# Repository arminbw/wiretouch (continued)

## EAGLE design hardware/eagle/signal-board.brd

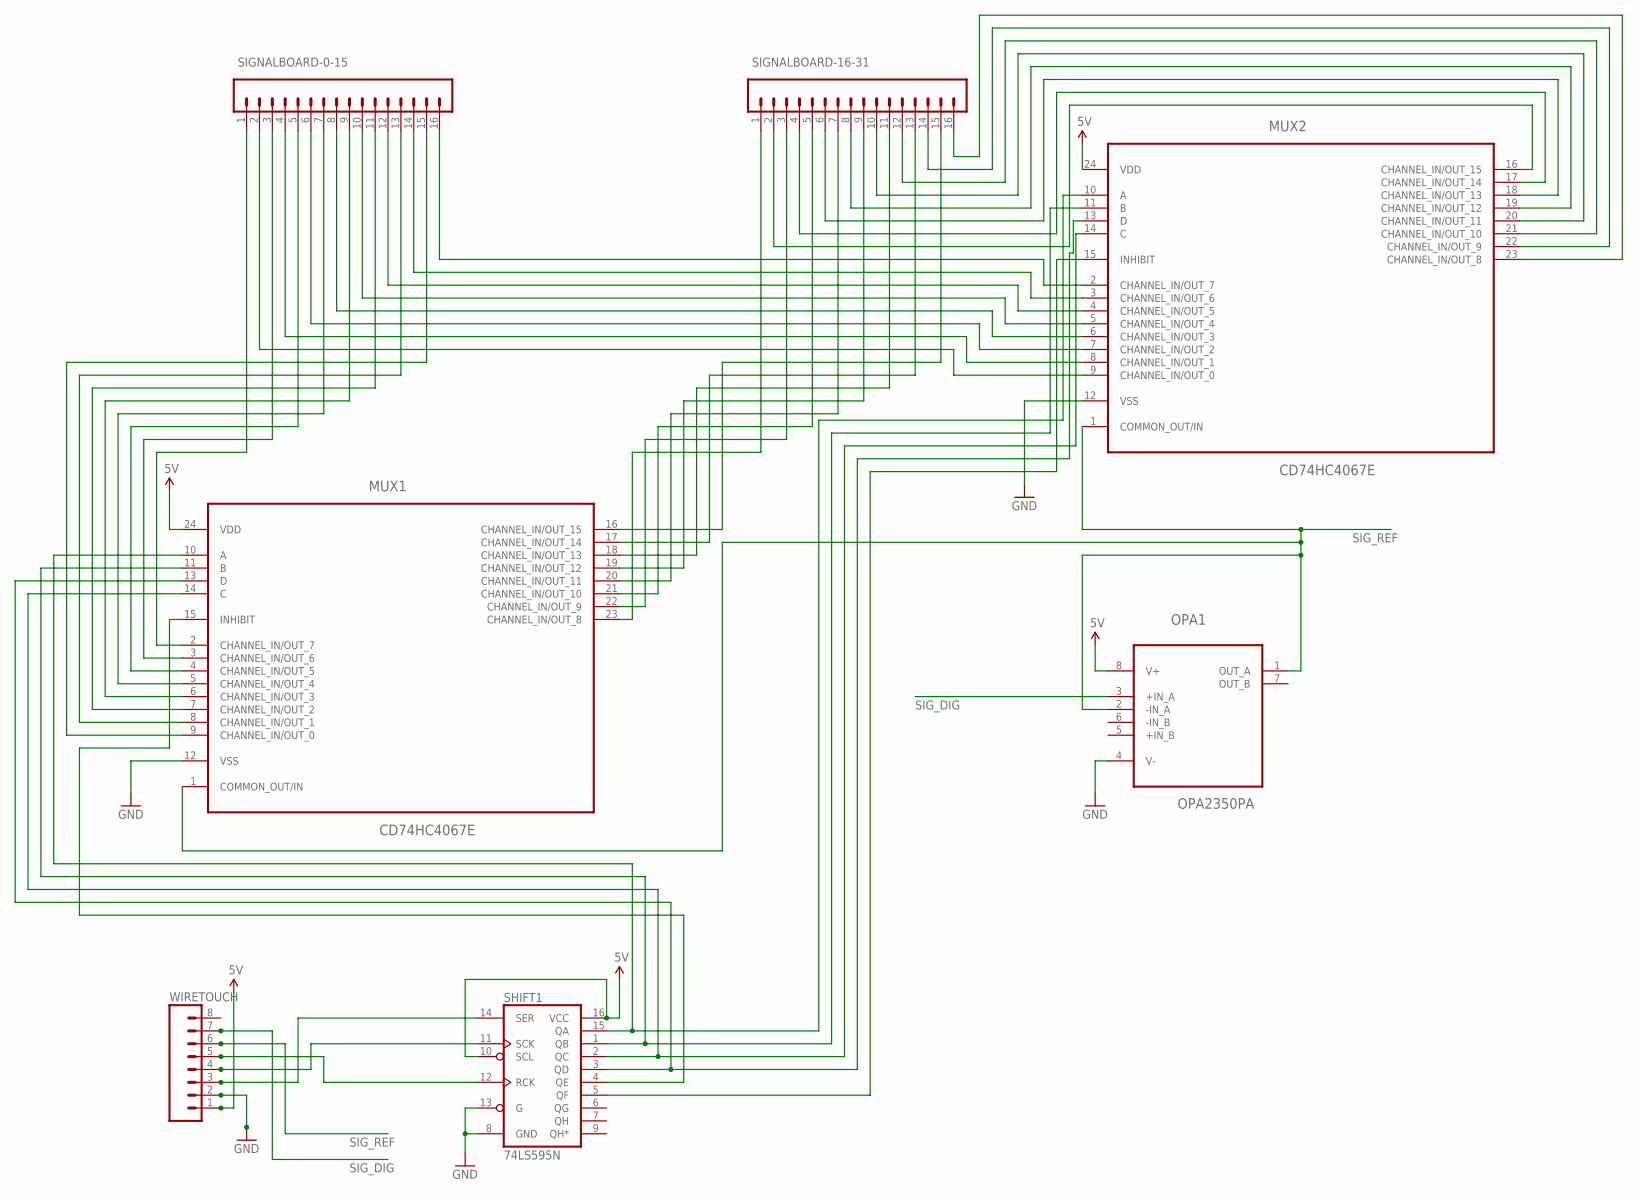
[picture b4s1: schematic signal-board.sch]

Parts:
MUX1, MUX2: CD74HC4067E; PDIP24-WIDE-CD74HC4067E
OPA1: OPA2350PA; DIP254P762X508-8
SHIFT1: 74LS595N; DIL16
SIGNALBOARD-0-15, SIGNALBOARD-16-31: M16LOCK_LONGPADS; 1X16_LOCK_LONGPADS
WIRETOUCH: M08LONGPADS; 1X08_LONGPADS

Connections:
5V: MUX1.24 (VDD), MUX2.24 (VDD), OPA1.8 (V+), SHIFT1.10 (SCL), SHIFT1.16 (VCC), WIRETOUCH.1
GND: MUX1.12 (VSS), MUX2.12 (VSS), OPA1.4 (V-), SHIFT1.8 (GND), SHIFT1.13 (G), WIRETOUCH.2
unnamed: MUX1.2 (CHANNEL_IN/OUT_7), SIGNALBOARD-0-15.1
unnamed: MUX1.3 (CHANNEL_IN/OUT_6), SIGNALBOARD-0-15.3
unnamed: MUX1.4 (CHANNEL_IN/OUT_5), SIGNALBOARD-0-15.5
unnamed: MUX1.5 (CHANNEL_IN/OUT_4), SIGNALBOARD-0-15.7
unnamed: MUX1.6 (CHANNEL_IN/OUT_3), SIGNALBOARD-0-15.9
unnamed: MUX1.7 (CHANNEL_IN/OUT_2), SIGNALBOARD-0-15.11
unnamed: MUX1.8 (CHANNEL_IN/OUT_1), SIGNALBOARD-0-15.13
unnamed: MUX1.9 (CHANNEL_IN/OUT_0), SIGNALBOARD-0-15.15
unnamed: MUX1.23 (CHANNEL_IN/OUT_8), SIGNALBOARD-16-31.1
unnamed: MUX1.22 (CHANNEL_IN/OUT_9), SIGNALBOARD-16-31.3
unnamed: MUX1.21 (CHANNEL_IN/OUT_10), SIGNALBOARD-16-31.5
unnamed: MUX1.20 (CHANNEL_IN/OUT_11), SIGNALBOARD-16-31.7
unnamed: MUX1.19 (CHANNEL_IN/OUT_12), SIGNALBOARD-16-31.9
unnamed: MUX1.18 (CHANNEL_IN/OUT_13), SIGNALBOARD-16-31.11
unnamed: MUX1.17 (CHANNEL_IN/OUT_14), SIGNALBOARD-16-31.13
unnamed: MUX1.16 (CHANNEL_IN/OUT_15), SIGNALBOARD-16-31.15
unnamed: MUX2.9 (CHANNEL_IN/OUT_0), SIGNALBOARD-0-15.2
unnamed: MUX2.8 (CHANNEL_IN/OUT_1), SIGNALBOARD-0-15.4
unnamed: MUX2.7 (CHANNEL_IN/OUT_2), SIGNALBOARD-0-15.6
unnamed: MUX2.6 (CHANNEL_IN/OUT_3), SIGNALBOARD-0-15.8
unnamed: MUX2.5 (CHANNEL_IN/OUT_4), SIGNALBOARD-0-15.10
unnamed: MUX2.4 (CHANNEL_IN/OUT_5), SIGNALBOARD-0-15.12
unnamed: MUX2.3 (CHANNEL_IN/OUT_6), SIGNALBOARD-0-15.14
unnamed: MUX2.2 (CHANNEL_IN/OUT_7), SIGNALBOARD-0-15.16
unnamed: MUX2.16 (CHANNEL_IN/OUT_15), SIGNALBOARD-16-31.2
unnamed: MUX2.17 (CHANNEL_IN/OUT_14), SIGNALBOARD-16-31.4
unnamed: MUX2.18 (CHANNEL_IN/OUT_13), SIGNALBOARD-16-31.6
unnamed: MUX2.19 (CHANNEL_IN/OUT_12), SIGNALBOARD-16-31.8
unnamed: MUX2.20 (CHANNEL_IN/OUT_11), SIGNALBOARD-16-31.10
unnamed: MUX2.21 (CHANNEL_IN/OUT_10), SIGNALBOARD-16-31.12
unnamed: MUX2.22 (CHANNEL_IN/OUT_9), SIGNALBOARD-16-31.14
unnamed: MUX2.23 (CHANNEL_IN/OUT_8), SIGNALBOARD-16-31.16
unnamed: MUX1.11 (B), MUX2.11 (B), SHIFT1.1 (QB)
unnamed: MUX1.10 (A), MUX2.10 (A), SHIFT1.15 (QA)
unnamed: MUX1.14 (C), MUX2.14 (C), SHIFT1.2 (QC)
unnamed: SHIFT1.14 (SER), WIRETOUCH.3
unnamed: MUX1.15 (INHIBIT), SHIFT1.4 (QE)
unnamed: MUX2.15 (INHIBIT), SHIFT1.5 (QF)
unnamed: SHIFT1.11 (SCK), WIRETOUCH.4
unnamed: MUX1.13 (D), MUX2.13 (D), SHIFT1.3 (QD)
unnamed: SHIFT1.12 (RCK), WIRETOUCH.5
SIG_DIG: OPA1.3 (+IN_A), WIRETOUCH.7
SIG_REF: MUX1.1 (COMMON_OUT/IN), MUX2.1 (COMMON_OUT/IN), OPA1.1 (OUT_A), OPA1.2 (-IN_A), WIRETOUCH.6

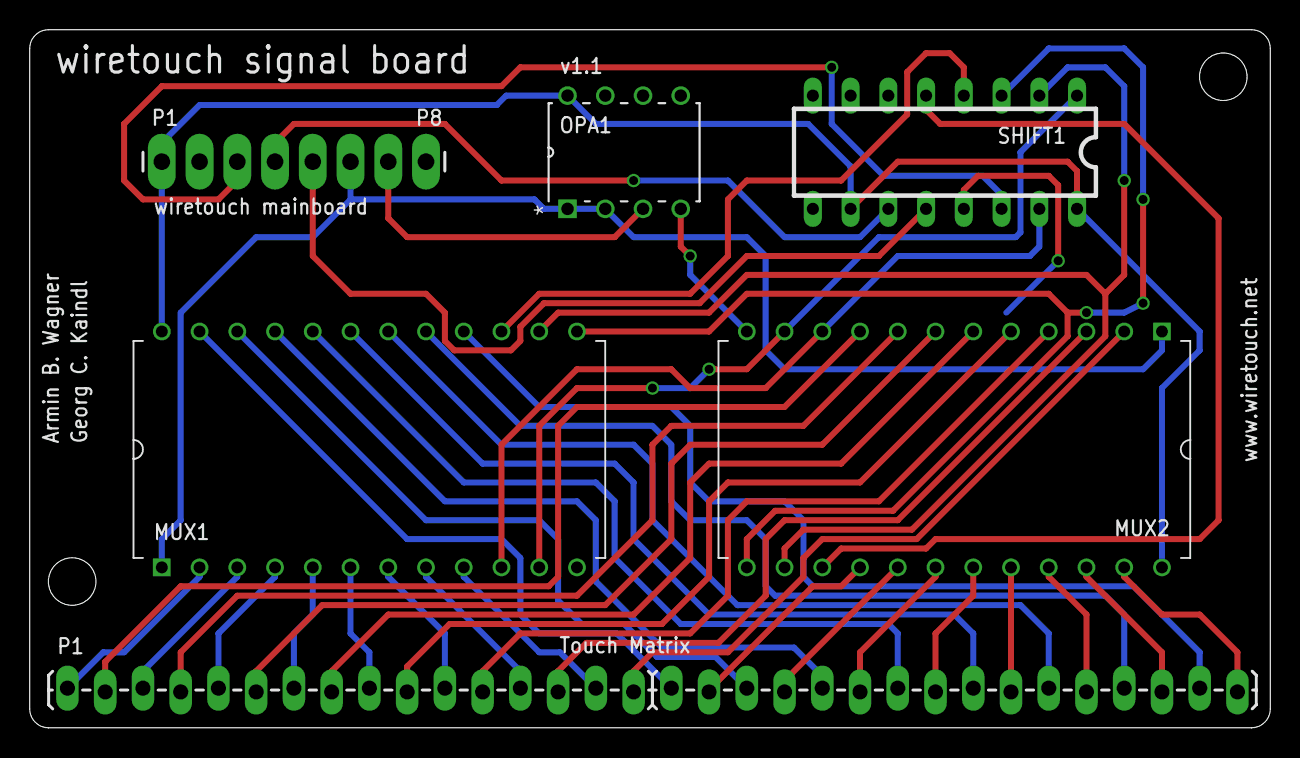
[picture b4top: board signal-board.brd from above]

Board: 4 copper layers, 83.5 x 47.0 mm, 7 parts (0 on the bottom side), 45 nets.

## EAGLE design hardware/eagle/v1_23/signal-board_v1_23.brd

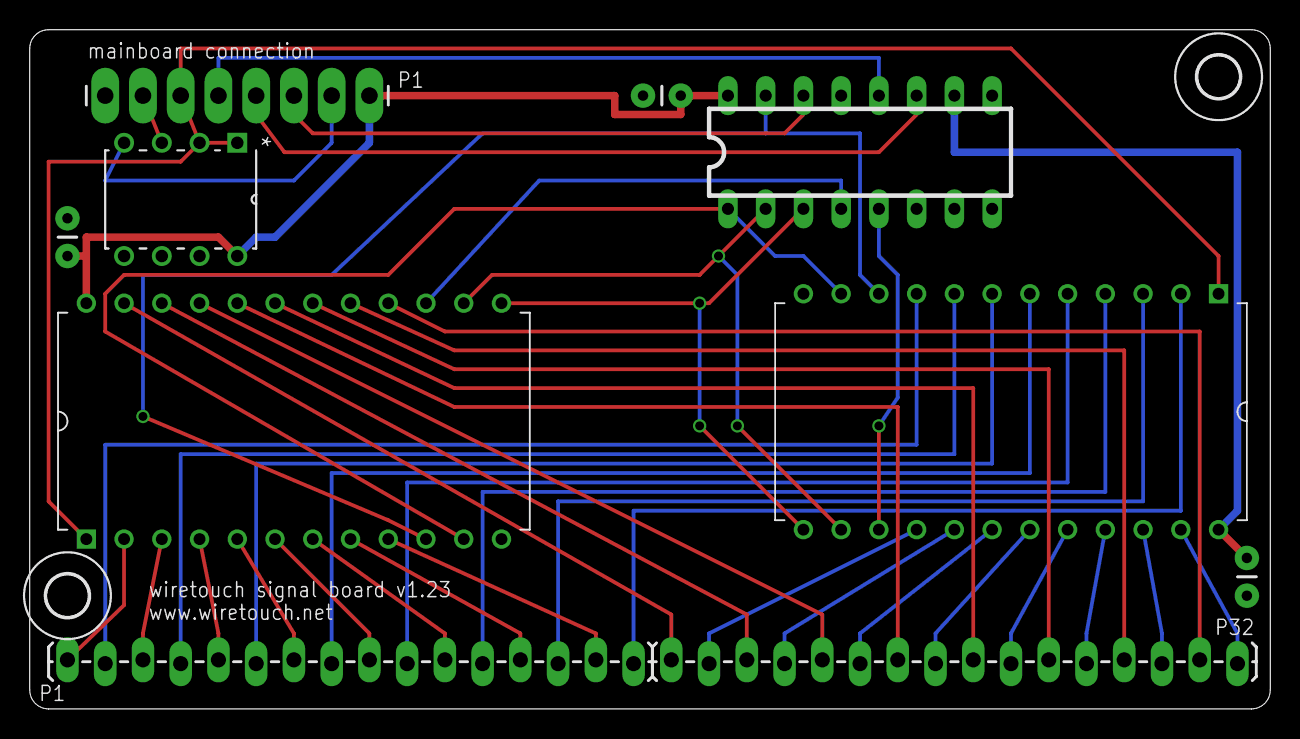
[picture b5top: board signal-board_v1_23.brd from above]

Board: 2 copper layers, 83.5 x 45.7 mm, 12 parts (0 on the bottom side), 45 nets.

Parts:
C2, C3, C4: 100nF; CAP-PTH-SMALL
MAINBOARD: MAINBOARD; 1X08_LONGPADS
MUX1, MUX2: CD74HC4067E; PDIP24-WIDE-CD74HC4067E
OPA1: OPA2350PA; DIP254P762X508-8
SENSORPANEL-0-15, SENSORPANEL-16-31: M16LOCK_LONGPADS; 1X16_LOCK_LONGPADS
SHIFT1: 74LS595N; DIL16
U$6, U$7: 2,8

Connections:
5V: C2.2, C3.2, C4.2, MAINBOARD.1, MUX1.24, MUX2.24, OPA1.8, SHIFT1.10, SHIFT1.16
GND: C2.1, C3.1, C4.1, MAINBOARD.2, MUX1.12, MUX2.12, OPA1.4, SHIFT1.8, SHIFT1.13
unnamed: MUX1.2, SENSORPANEL-0-15.1
unnamed: MUX1.3, SENSORPANEL-0-15.3
unnamed: MUX1.4, SENSORPANEL-0-15.5
unnamed: MUX1.5, SENSORPANEL-0-15.7
unnamed: MUX1.6, SENSORPANEL-0-15.9
unnamed: MUX1.7, SENSORPANEL-0-15.11
unnamed: MUX1.8, SENSORPANEL-0-15.13
unnamed: MUX1.9, SENSORPANEL-0-15.15
unnamed: MUX1.23, SENSORPANEL-16-31.1
unnamed: MUX1.22, SENSORPANEL-16-31.3
unnamed: MUX1.21, SENSORPANEL-16-31.5
unnamed: MUX1.20, SENSORPANEL-16-31.7
unnamed: MUX1.19, SENSORPANEL-16-31.9
unnamed: MUX1.18, SENSORPANEL-16-31.11
unnamed: MUX1.17, SENSORPANEL-16-31.13
unnamed: MUX1.16, SENSORPANEL-16-31.15
unnamed: MUX2.9, SENSORPANEL-0-15.2
unnamed: MUX2.8, SENSORPANEL-0-15.4
unnamed: MUX2.7, SENSORPANEL-0-15.6
unnamed: MUX2.6, SENSORPANEL-0-15.8
unnamed: MUX2.5, SENSORPANEL-0-15.10
unnamed: MUX2.4, SENSORPANEL-0-15.12
unnamed: MUX2.3, SENSORPANEL-0-15.14
unnamed: MUX2.2, SENSORPANEL-0-15.16
unnamed: MUX2.16, SENSORPANEL-16-31.2
unnamed: MUX2.17, SENSORPANEL-16-31.4
unnamed: MUX2.18, SENSORPANEL-16-31.6
unnamed: MUX2.19, SENSORPANEL-16-31.8
unnamed: MUX2.20, SENSORPANEL-16-31.10
unnamed: MUX2.21, SENSORPANEL-16-31.12
unnamed: MUX2.22, SENSORPANEL-16-31.14
unnamed: MUX2.23, SENSORPANEL-16-31.16
unnamed: MUX1.11, MUX2.11, SHIFT1.1
unnamed: MUX1.10, MUX2.10, SHIFT1.15
unnamed: MUX1.14, MUX2.14, SHIFT1.2
unnamed: MAINBOARD.3, SHIFT1.14
unnamed: MUX1.15, SHIFT1.4
unnamed: MUX2.15, SHIFT1.5
unnamed: MAINBOARD.4, SHIFT1.11
unnamed: MUX1.13, MUX2.13, SHIFT1.3
unnamed: MAINBOARD.5, SHIFT1.12
SIG_DIG: MAINBOARD.7, OPA1.3
SIG_REF: MAINBOARD.6, MUX1.1, MUX2.1, OPA1.1, OPA1.2

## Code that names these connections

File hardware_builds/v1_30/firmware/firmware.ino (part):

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  sbi(ADCSRA, ADPS1);
  cbi(ADCSRA, ADPS0);

  pinMode(2, OUTPUT);     // CS for SPI pot 1 (halfwave splitting)        PD2
  pinMode(3, OUTPUT);     // reference signal OUT                         PD3
  pinMode(4, OUTPUT);     // CS for SPI pot 2 (output amplifier)          PD4
  pinMode(6, OUTPUT);     // horizontal lines (sensor) shift reg latch    PD6
  pinMode(9, OUTPUT);     // vertical lines (signal) shift reg latch      PB1
  pinMode(A1, OUTPUT);    // maximum "sample and hold" RESET switch       PC1

  SPI.setBitOrder(MSBFIRST);
  SPI.setClockDivider(SPI_CLOCK_DIV2);
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
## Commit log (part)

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2011-06-04 initial commit: 2 crosspoints prototype code
2011-06-04 cleanup
2011-06-07 processing sketch now more scaleable
2011-06-07 single board mux
2011-06-10 First tests with 4 crosspoints.
2011-06-17 first test with 2 rows (16 crosspoints)
2011-06-20 small measurement changes
2011-06-22 Experimenting More debug output & third sensor row
2011-06-28 more experiments
2011-06-29 even more experiments
2011-07-01 48 crosspoints demo
2011-07-01 bugfix: array indexing
2011-07-12 searching bug: row order wrong
2011-07-14 176 crosspoints
2011-07-14 sketch refactoring
2011-07-14 linear interpolation pixel matrix test
2011-07-27 some refactoring (datamanager.pde) and new fake data (my hand)
2011-07-28 more flexible interpolation architecture, better pixel-grid rendering, multiple interpolation algorithms
    linear, cosine, cubic, catmull-rom, hermite
2011-08-01 cleanup, minor ui changes
2011-08-05 contrast stretching via histogram
2011-08-05 draw histogram distribution (logarithmic scale)
2011-08-05 editable histogram left/right cutoff for contrast stretch
2011-08-05 histogram gui elements
2011-08-08 ui related code adjustments
2011-08-08 bugfix: contrast settings
2011-08-12 minor visualization adjustments
2011-08-12 increased delay to deal with row-bug
2011-09-15 Double-Mux + ShiftReg test
2011-09-17 more crosspoints, testing shift register
2011-09-18 minor visualization changes
2011-09-19 new fake data
2011-10-20 blob detection experiments
2011-10-21 arduino code: faster measurements (writes to ports directory instead of using arduino core convenience functions).
2011-10-21 speed measurements
2011-10-21 10-bit packed sending of sensor data.
2011-10-21 incredibly minor fps counter bugfix.
2011-10-27 shift register bug fix
2011-10-31 some refactoring
2011-11-01 testing GLGraphics
2011-11-02 less CPU load due to GLGraphics
2011-11-02 fixed some new bugs
2011-11-23 some blob experiments, several minor fixes
2011-11-25 minor bug fix
2012-01-05 changed one set of multiplexer pins from 2,3.4 to 8,9,10
2012-01-05 sampling done from interrupt triggered by reference signal.
2012-01-11 trying to reduce noise
2012-01-19 minor edits (prototype working again)
2012-01-20 pin/port changes
2012-01-20 attempt to implement measuring via PCM1308 adc.
2012-01-20 experiments with the pcm1308
2012-01-27 since spi is enabled now, pin 5 is used instead of pin 12 for peak detection
2012-02-23 unit testing
2012-02-29 tracking serial buffer bug
2012-03-16 minor edits (fps hunt)
2012-03-26 minor edits
2012-03-26 debugging draw/SerialEvent timing problems
2012-04-06 further experiments with the pcm1803
2012-04-13 buffered send_packed10.
2012-04-13 improved buffered send_packed10.
2012-04-13 buffer experiments
2012-04-17 buffer debugging
2012-04-18 serialcom visualization
2012-04-20 last cable grid prototype
2012-04-27 kalman
2012-05-04 tracking experiments with the flob lib
2012-05-25 switch to new mux (74hc4051)
2012-06-01 mux switch bug search
2012-06-15 equalized
2012-08-06 several minor changes (we are trying to fix the mux signal distortion)
2012-08-10 added invertible cipher function to map measurement coordinates.
2012-08-10 added invertible cipher to processing sketch as well.
2012-08-11 processing app to test different measurement mapping functions.
2012-08-17 cleaned up sensor code and changed muxSPI code back to our old 16-channel mixes.
2012-08-30 Georg didn't commit his changes. :(
2012-09-07 testing blob libraries again
2012-09-07 using Flob tracking and signalCutOff
2012-09-07 tuio.
2012-09-07 tuio server
2012-10-05 updated the fakeHand
2012-10-05 attempting adaptive background subtraction.
2012-10-05 adaptive background substraction
2012-10-05 reinserted important line
2012-11-02 peter's cross idea.
2012-11-09 breakthrough! (removed Georg's special signal-distribution algorithm)
2012-12-14 pin changes for pcb layout
2013-05-10 trying to fix the vertical lines
2013-05-10 quick fix to get a few more GUI sliders (this code needs some serious refactoring)
2013-05-10 controlling the digital pot
2013-05-17 cleaned arduino firmware + a TODO.
2013-05-17 added support for second poti to firmware.
2013-05-17 slider for every single crosspoint
2013-05-17 digital halfwave and outputamp pots
2013-05-17 trivial output amp auto-tuning.
2013-05-17 autotuning all the dots
2013-05-24 one more slider
2013-05-24 in-firmware calibration
2013-06-14 minor changes
2013-06-14 minor changes (starting to clean up)
2013-06-21 calibration improved
2013-06-21 began implementation of openframeworks monitoring app.
2013-06-28 dicking around with the FTDI serial driver settings on MacOS X – seems to be solved now and running fine at 500000bps. Needs driver hack, will write script for that soon.
2013-07-12 added perl script to patch FTDI driver info.plist to support 500000 baud (aliased to 300baud) transfer for FTDI R series (required for fast framerate).
2013-07-12 patch ftdi info.plist: ask to disconnect all FTDI devices first and only reload kext if it is currently loaded.
2013-07-12 added missing newline.
2013-07-12 processing on OSX ftdi hack (see also: modify-ftdi-driver-settings.pl)
2013-07-12 adding ofxUI
2013-07-12 gui stuff
2013-07-12 more gui tests
2013-07-12 font added
2013-07-12 began re-implementing our interpolation methods in open frameworks.
2013-07-19 "interpolator" ported to openframeworks client.
2013-07-19 GUI experiments
2013-07-19 more gui experiments
2013-07-19 nothing to see here :-/
2013-08-02 ported our interpolators from previous processing code & added convenience method to switch to different interpolator settings.
2013-08-02 interpolation pulldown menu
2013-08-02 gui changes
2013-08-02 readme.md
2013-08-02 added weighted nearest neighbour interpolator.
2013-08-02 added lagrange interpolator.
2013-08-02 more gui
2013-08-02 gui changes: more interpolation types
2013-08-04 more gui changes
2013-08-16 typo
2013-08-16 gui bug fix
2013-08-16 began implementing blob tracking functionality.
2013-08-16 minor gui changes
2013-08-23 prevent gui title bar from leaving the app window. also: new slider for blob visualization.
2013-08-23 visualising the thresholded image.
2013-08-23 additional settings for adaptive thresholding + a setting to apply a greyscale gamma to the data read from the sensor.
2013-08-23 cleaning up. licensing.
2013-08-23 more licensing
2013-08-23 minor gui change (gui shouldn't leave the window)
2013-08-23 added TUIO output (currently hardcoded to localhost, port 3333).
2013-08-30 blob minimum area now dependent on current sensor image dimensions.
2013-09-06 firmware: added command to stop the transmission of sensor data.
2013-09-06 calibrate button, start/stop button, timing recovery after window resize
    there is now a separate "calibrate" button to call the calibration program. the start button will turn into a stop button while the tracker is running. also, the sensor will automatically recover the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
2013-09-06 added an fps label (e.g. tracking the amount of sensor packets received per second).
2013-09-06 show "calibrating…" as button label while the calibration process is running & show proper interpolation type as label when the app is launched.
2013-09-06 added display label for firmware version.
2013-10-18 tracked blob centroid is now re-calculcated based on the weighted average of pixel intensities within the blob bounding box. this greatly increases accuracy.
2013-12-06 improved firmware default values & updated calibration algorithm.
2013-12-28 modifications for Xcode5 and openFrameworks 0.8.0 on OSX 10.9
    - I undid our changes in ofTypes.h and used the oF 0.8.0 project builder to
    set up a new, clean project. No "tr1/memory file not found" error.
    Works with the 10.9 Base SDK.
    - Several oF libs are 32-bit-only builds. I set the project build setting
    "Architectures" to "32-bit Intel".
    - I let Xcode find all header files by setting "User Header Search Paths" to
2014-01-03 added macro definition of OF_KEY_CTRL to xcode build settings, because this is apparently missing in ofxUI for whatever reason.
2014-01-24 minor changes: blob detection gui
2014-01-31 started to add a GUI for serial port selection. corrected some licence typos.
2014-01-31 send gui-visible settings to board when the serial connection is established.
2014-02-14 testing performance and redrawing
2014-02-14 send only TUIO data when serial buffer consumed
2014-02-14 enlarge the tuneable range of tracking parameters for improved detector output.
2014-05-02 experimental measurement scaling via a lut generated from a parametrized exp() function.
2014-05-02 frequency slider now shows the actual frequency value. also added settings for the measurement LUT transform.
2014-10-30 updated project files to xcode 6.1 (OSX 10.10)
2014-10-31 we all love readme files
2014-10-31 more instructions
2014-11-03 more documentation
2014-11-03 .gitignore updated
2014-11-05 ofxUIDropDownList has issues (see: https://github.com/rezaali/ofxUI/issues/68 ) The current implementation uses a self-made "modern" disclosure menu as a workaround.
2014-11-06 cleaned up GUI behavior. problem with serial connection.
2014-11-07 some refactoring. clean up. serial issues seem to be kext related.
2014-11-11 More cleanup. Changed the GUI-state logic a bit.
2014-11-11 minor GUI changes and typo corrections
2014-11-13 minor GUI fixes removed unnecessary ofxui assets
2014-11-14 ofxui+ofxXmlSettings don't store the values of ofxUIDropDownList correctly. storing settings now by using cjson. might need some refactoring later on.
2014-11-15 json-data transfer via serial connection works again, but needs more love.
2014-11-16 color adjustment
2014-11-16 check if settings.json exists
2014-11-18 minor changes: * don't send all parameters after calibration * activate blob tracking boolean after loadsettings()
2014-11-18 don't send all parameters after calibration
2014-11-23 minor GUI adjustments: * upsampling slider doesn't create jitter * blob detection state loads correctly testing portrait-mode sensor matrix
2015-02-18 added the board schematics and CAD files
2016-04-01 added the sensor plate gerber files we designed for the audio-tactile map
2016-04-16 * minor modification of the firmware.ino file to make the updated * Arduino IDE preprocesser work (fixes the "was not declared in this scope" * errors) * updated the README file * switching to Xcode 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
2016-04-16 this extra header search path is not needed
2016-04-16 minor stylistic changes
2016-04-16 corrected the Markdown formatted hyperlinks
2016-05-01 Cleaning up the motherboard schematic in order to get a better overview. No functional changes.
2016-05-05 The motherboard's schematic was missing a connection (OUT_B to R19 and the switch's S3). We fixed this using a short wire, but forgot to update the eagle files. Many thanks to Mike Farr for pointing 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
2016-05-06 The motherboard version 1.21 includes the missing connection on the OPA2350-5. I also worked a bit on the routing and added a printout of the schematics.
2016-05-07 cosmetic changes on the signal-board schematic putting the 1.21 version in a seperate directory
2016-05-08 adding a cleaned up version of the sensor-board
2016-05-29 Corrected an error in the signal board schematic. GND was connected to OPA1's +IN_B.
2016-06-26 wiretouch hardware v1.23 added a few decoupling capacitors new board layout
2016-06-26 minor aesthetic change
2016-09-01 clean up
2016-09-03 hardware build v1.3: * I exchanged the 74HC4067 multiplexers with MAX306CPI+ multiplexers. * I simplified the signal board's connection to the sensor panel: no more criss-crossing. Pin 1-16 belong to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
2016-09-04 minor adjustment of the GUI frequency formula. removed a few comment.
2016-09-04 added a compiled version (OSX 10.11) of wiretouch_monitor
2017-04-06 minor markdown header correction
    see: https://github.com/github/markup/issues/1013
2017-06-11 removed debugging messages adjusted muxSPI vertical mapping
2017-06-11 The patched FTDI driver isn't working in OSX 10.12.5
    While I am trying to figure out what is going on, please use the
    default driver (com.apple.driver.AppleUSBFTDI).
    I have reduced the symbol rate accordingly to Apple's maximum, which is 115200 BAUD.
    This reduces the framerate to ca. 11 fps. :(
2017-06-11 FTDI driver is causing troubles
2017-06-18 reduced BAUD
2018-10-12 Added documentation. Updated README.md
2020-05-23 Updated the readme file.
